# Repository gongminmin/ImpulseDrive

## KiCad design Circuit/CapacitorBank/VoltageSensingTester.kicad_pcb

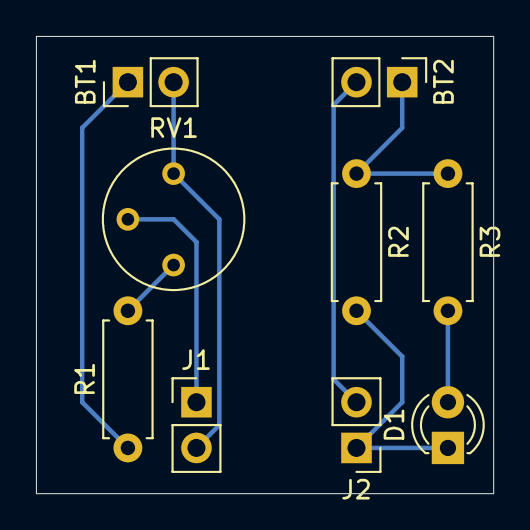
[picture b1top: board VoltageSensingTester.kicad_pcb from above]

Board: 2 copper layers, 25.4 x 25.4 mm, 9 parts (0 on the bottom side), 8 nets.

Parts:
BT1, BT2: Battery; PinHeader_1x02_P2.54mm_Vertical
D1: LED; LED_D3.0mm_FlatTop
J1, J2: Conn_01x02_Male; PinHeader_1x02_P2.54mm_Vertical
R1: 10K; R_Axial_DIN0207_L6.3mm_D2.5mm_P7.62mm_Horizontal
R2: 3.3K; R_Axial_DIN0207_L6.3mm_D2.5mm_P7.62mm_Horizontal
R3: 2K; R_Axial_DIN0207_L6.3mm_D2.5mm_P7.62mm_Horizontal
RV1: 50K; Potentiometer_Bourns_3339P_Vertical

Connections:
unnamed: BT1.1, R1.1
unnamed: BT1.2, J1.2, RV1.3
unnamed: BT2.1, R2.1, R3.1
unnamed: BT2.2, J2.2
unnamed: D1.1, J2.1, R2.2
unnamed: D1.2, R3.2
unnamed: J1.1, RV1.2
unnamed: R1.2, RV1.1

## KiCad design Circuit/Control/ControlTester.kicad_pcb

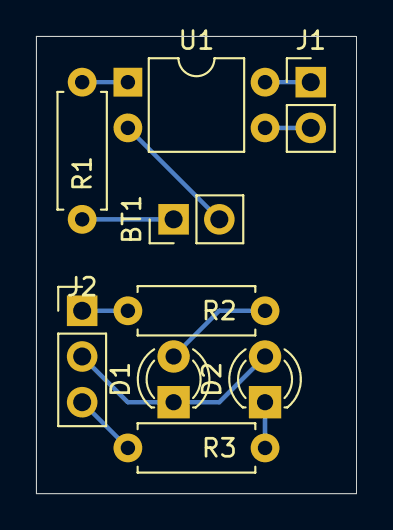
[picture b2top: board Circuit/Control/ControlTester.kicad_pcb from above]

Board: 2 copper layers, 17.8 x 25.4 mm, 9 parts (0 on the bottom side), 10 nets.

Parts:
BT1: 12V Battery; PinHeader_1x02_P2.54mm_Vertical
D1, D2: LED; LED_D3.0mm_FlatTop
J1: Signal; PinHeader_1x02_P2.54mm_Vertical
J2: 12V NO G; PinHeader_1x03_P2.54mm_Vertical
R1: 1K; R_Axial_DIN0207_L6.3mm_D2.5mm_P7.62mm_Horizontal
R2, R3: 2K2; R_Axial_DIN0207_L6.3mm_D2.5mm_P7.62mm_Horizontal
U1: PC817; DIP-4_W7.62mm

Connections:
unnamed: BT1.1, R1.1
unnamed: BT1.2, U1.2
unnamed: D1.1, D2.2, J2.2
unnamed: D1.2, R2.2
unnamed: D2.1, R3.2
unnamed: J1.1, U1.4
unnamed: J1.2, U1.3
unnamed: J2.1, R2.1
unnamed: J2.3, R3.1
unnamed: R1.2, U1.1

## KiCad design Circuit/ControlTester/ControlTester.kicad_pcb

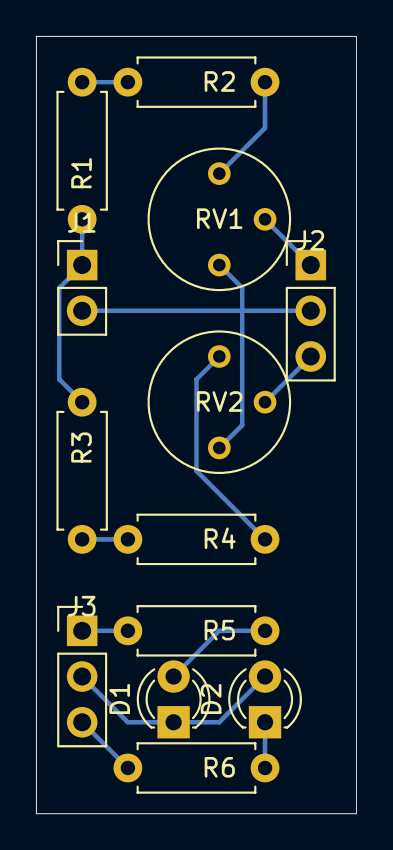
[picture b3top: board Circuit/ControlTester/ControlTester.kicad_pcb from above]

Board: 2 copper layers, 17.8 x 43.2 mm, 13 parts (0 on the bottom side), 13 nets.

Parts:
D1, D2: LED; LED_D3.0mm_FlatTop
J1: Power; PinHeader_1x02_P2.54mm_Vertical
J2: Signal; PinHeader_1x03_P2.54mm_Vertical
J3: 12V NO G; PinHeader_1x03_P2.54mm_Vertical
R1, R2, R3, R4: 20K; R_Axial_DIN0207_L6.3mm_D2.5mm_P7.62mm_Horizontal
R5, R6: 2K2; R_Axial_DIN0207_L6.3mm_D2.5mm_P7.62mm_Horizontal
RV1, RV2: 50K; Potentiometer_Bourns_3339P_Vertical

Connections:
+12V: J1.1, R1.1, R3.1
GND: J1.2, J2.2, RV1.3, RV2.3
unnamed: D1.1, D2.2, J3.2
unnamed: D1.2, R5.2
unnamed: D2.1, R6.2
unnamed: J2.1, RV1.2
unnamed: J2.3, RV2.2
unnamed: J3.1, R5.1
unnamed: J3.3, R6.1
unnamed: R1.2, R2.1
unnamed: R2.2, RV1.1
unnamed: R3.2, R4.1
unnamed: R4.2, RV2.1

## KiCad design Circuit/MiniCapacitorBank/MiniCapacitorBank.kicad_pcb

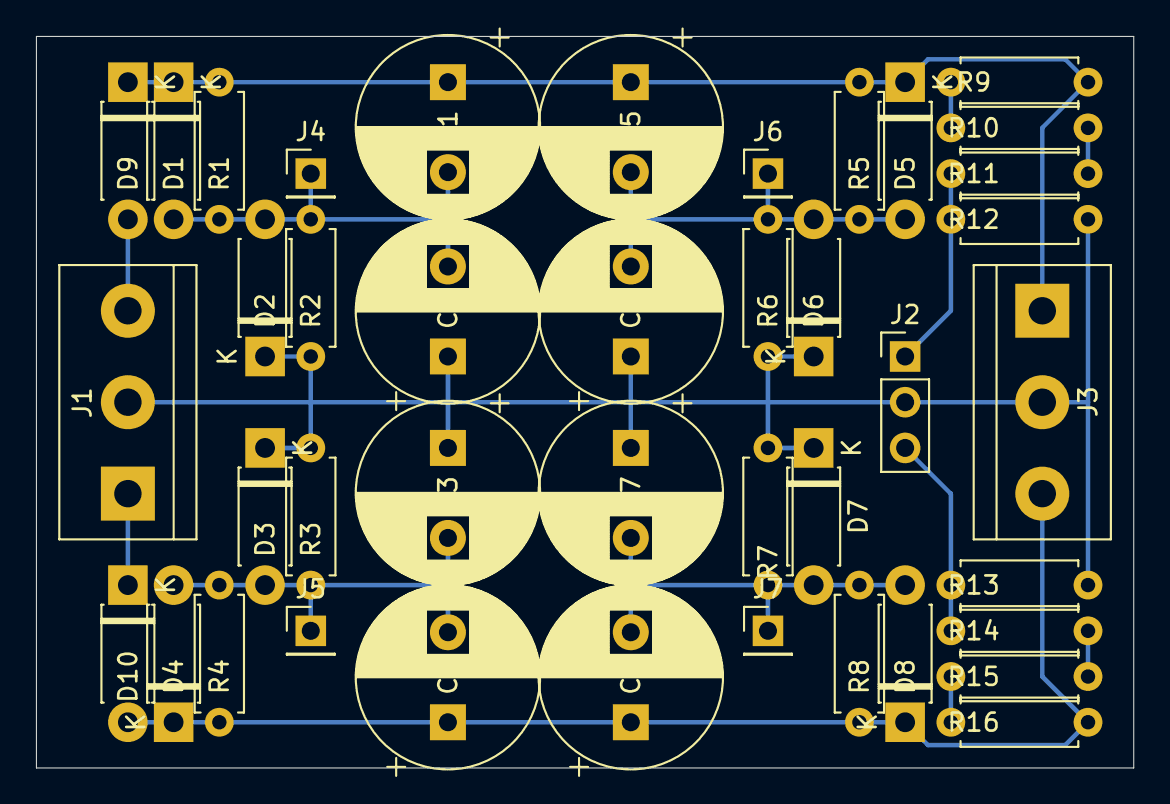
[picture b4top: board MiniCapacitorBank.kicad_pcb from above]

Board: 2 copper layers, 61.0 x 40.6 mm, 41 parts (0 on the bottom side), 15 nets.

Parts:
C1, C2, C3, C4, C5, C6, C7, C8: 330uF; CP_Radial_D10.0mm_P5.00mm
D1, D2, D3, D4, D5, D6, D7, D8, D9, D10: 1N4007; D_DO-41_SOD81_P7.62mm_Horizontal
J1: +-45V in; TerminalBlock_bornier-3_P5.08mm
J2: To Feedback; PinHeader_1x03_P2.54mm_Vertical
J3: +-45V out; TerminalBlock_bornier-3_P5.08mm
J4: Signal 1; PinHeader_1x01_P2.54mm_Vertical
J5: Signal 2; PinHeader_1x01_P2.54mm_Vertical
J6: Signal 3; PinHeader_1x01_P2.54mm_Vertical
J7: Signal 4; PinHeader_1x01_P2.54mm_Vertical
R1, R2, R3, R4, R5, R6, R7, R8: 1M; R_Axial_DIN0207_L6.3mm_D2.5mm_P7.62mm_Horizontal
R9, R16: 100K; R_Axial_DIN0207_L6.3mm_D2.5mm_P7.62mm_Horizontal
R10, R12, R13, R15: 20K; R_Axial_DIN0207_L6.3mm_D2.5mm_P7.62mm_Horizontal
R11, R14: 3K3; R_Axial_DIN0207_L6.3mm_D2.5mm_P7.62mm_Horizontal

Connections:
+VDC: D9.2, J1.3
-VDC: D10.1, J1.1
GND: C2.1, C3.1, C6.1, C7.1, D2.1, D3.1, D6.1, D7.1, J1.2, J2.2, J3.2, R2.2, R3.1, R6.2, R7.1, R12.2, R13.1
unnamed: C1.1, C5.1, D1.1, D5.1, D9.1, J3.1, R1.1, R5.1, R9.1
unnamed: C1.2, C2.2, D1.2, D2.2, J4.1, R1.2, R2.1
unnamed: C3.2, C4.2, D3.2, D4.2, J5.1, R3.2, R4.1
unnamed: C4.1, C8.1, D4.1, D8.1, D10.2, J3.3, R4.2, R8.2, R16.1
unnamed: C5.2, C6.2, D5.2, D6.2, J6.1, R5.2, R6.1
unnamed: C7.2, C8.2, D7.2, D8.2, J7.1, R7.2, R8.1
unnamed: J2.1, R11.2, R12.1
unnamed: J2.3, R13.2, R14.2
unnamed: R9.2, R10.1
unnamed: R10.2, R11.1
unnamed: R14.1, R15.2
unnamed: R15.1, R16.2

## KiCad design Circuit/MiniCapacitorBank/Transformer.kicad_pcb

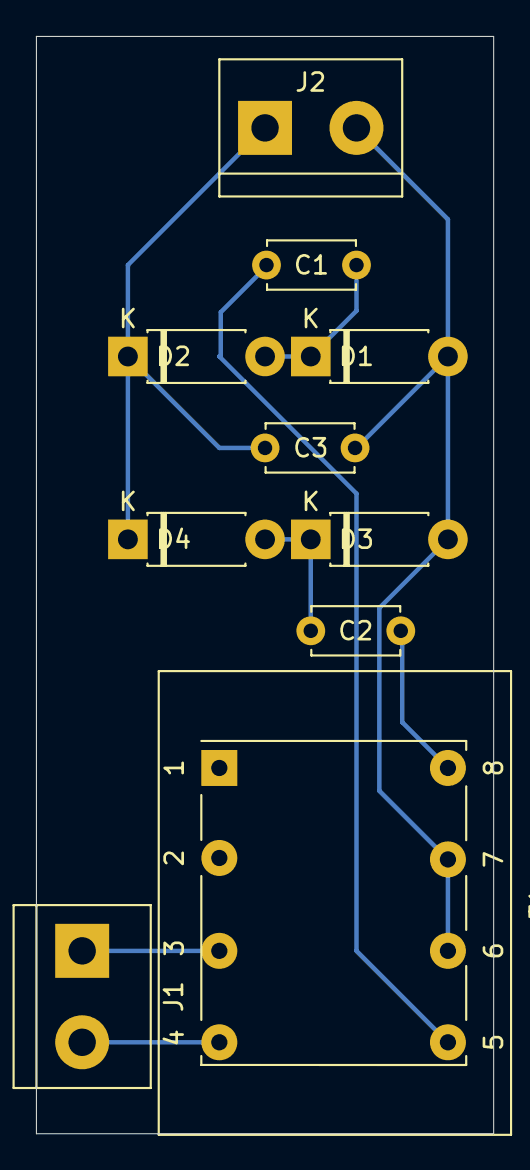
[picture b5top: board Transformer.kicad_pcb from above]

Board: 2 copper layers, 25.4 x 61.0 mm, 10 parts (0 on the bottom side), 8 nets.

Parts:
C1, C2, C3: 1nF; C_Disc_D4.7mm_W2.5mm_P5.00mm
D1, D2, D3, D4: 1N4007; D_DO-41_SOD81_P7.62mm_Horizontal
J1: AC Power In; TerminalBlock_bornier-2_P5.08mm
J2: To Capacitors; TerminalBlock_bornier-2_P5.08mm
T1: 6:200; Transformer_Generic_EE25_8Pin

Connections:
/ACPowerIn+: J1.1, T1.3
/ACPowerIn-: J1.2, T1.4
/CapacitorPower+: C3.1, D2.1, D4.1, J2.1
/CapacitorPower-: C3.2, D1.2, D3.2, J2.2, T1.6, T1.7
unnamed: C1.1, D1.1, D2.2
unnamed: C1.2, T1.5
unnamed: C2.1, D3.1, D4.2
unnamed: C2.2, T1.8

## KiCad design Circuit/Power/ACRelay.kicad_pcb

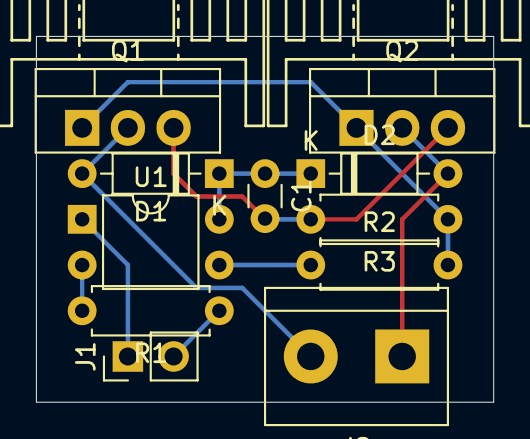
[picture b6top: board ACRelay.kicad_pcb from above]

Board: 2 copper layers, 25.4 x 20.3 mm, 13 parts (0 on the bottom side), 9 nets.

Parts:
C1: 0.1uF; C_Disc_D3.0mm_W1.6mm_P2.50mm
D1, D2: 1N4148; D_DO-35_SOD27_P7.62mm_Horizontal
HS1, HS2: Heatsink; Heatsink_TO220_15x10mm
J1: Input; PinHeader_1x02_P2.54mm_Vertical
J2: Output; TerminalBlock_bornier-2_P5.08mm
Q1, Q2: RFP30N06LE; TO-220-3_Vertical
R1: 1K; R_Axial_DIN0207_L6.3mm_D2.5mm_P7.62mm_Horizontal
R2, R3: 10K; R_Axial_DIN0207_L6.3mm_D2.5mm_P7.62mm_Horizontal
U1: PC817; DIP-4_W7.62mm

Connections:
/Input+: J1.1, U1.1
/Input-: J1.2, R1.1
/Output1: D1.2, J2.2, Q1.2
/Output2: D2.2, J2.1, Q2.2
unnamed: C1.1, D1.1, D2.1, U1.4
unnamed: C1.2, Q1.3, Q2.3, R3.2
unnamed: Q1.1, Q2.1, R2.2, R3.1
unnamed: R1.2, U1.2
unnamed: R2.1, U1.3

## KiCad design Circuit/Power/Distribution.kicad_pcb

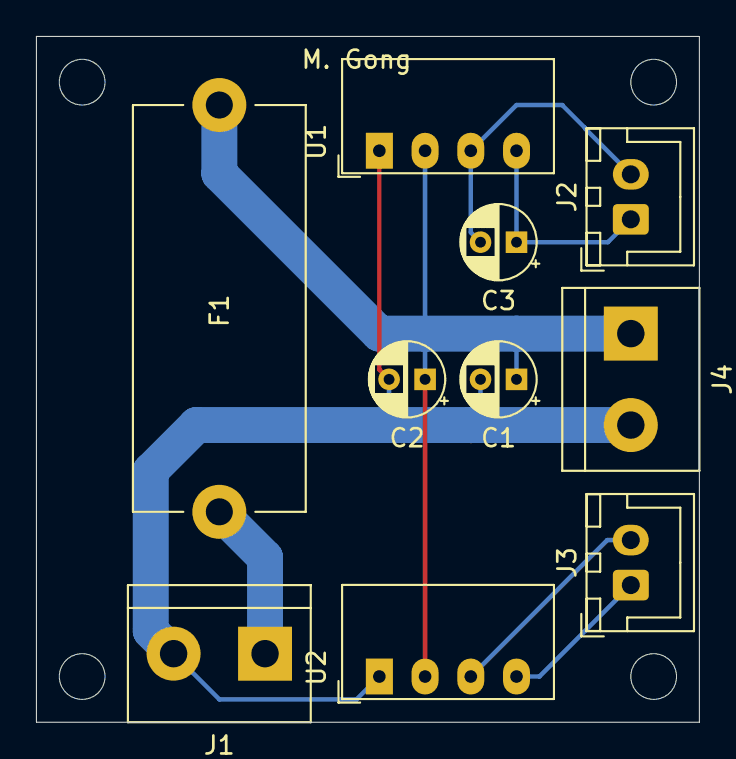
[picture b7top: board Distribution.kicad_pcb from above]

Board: 2 copper layers, 36.8 x 38.1 mm, 10 parts (0 on the bottom side), 7 nets.

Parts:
C1: 10uF; CP_Radial_D4.0mm_P2.00mm
C2, C3: 2.2uF; CP_Radial_D4.0mm_P2.00mm
F1: Fuse; Fuseholder_Cylinder-5x20mm_Stelvio-Kontek_PTF78_Horizontal_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
J1: Main Power In; TerminalBlock_bornier-2_P5.08mm
J2: To Control Power; JST_XH_B2B-XH-A_1x02_P2.50mm_Vertical
J3: To Coil; JST_XH_B2B-XH-A_1x02_P2.50mm_Vertical
J4: To Switch; TerminalBlock_bornier-2_P5.08mm
U1, U2: CRE1S1212SC; Converter_DCDC_muRata_CRE1xxxxxxSC_THT

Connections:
/CoilPower+: J3.1, U2.4
/CoilPower-: J3.2, U2.3
/ControlPower+: C3.1, J2.1, U1.4
/ControlPower-: C3.2, J2.2, U1.3
/PowerIn+: F1.2, J1.1
/PowerIn-: C1.2, C2.2, J1.2, J4.2, U1.1, U2.1
/SwitchPower+: C1.1, C2.1, F1.1, J4.1, U1.2, U2.2
